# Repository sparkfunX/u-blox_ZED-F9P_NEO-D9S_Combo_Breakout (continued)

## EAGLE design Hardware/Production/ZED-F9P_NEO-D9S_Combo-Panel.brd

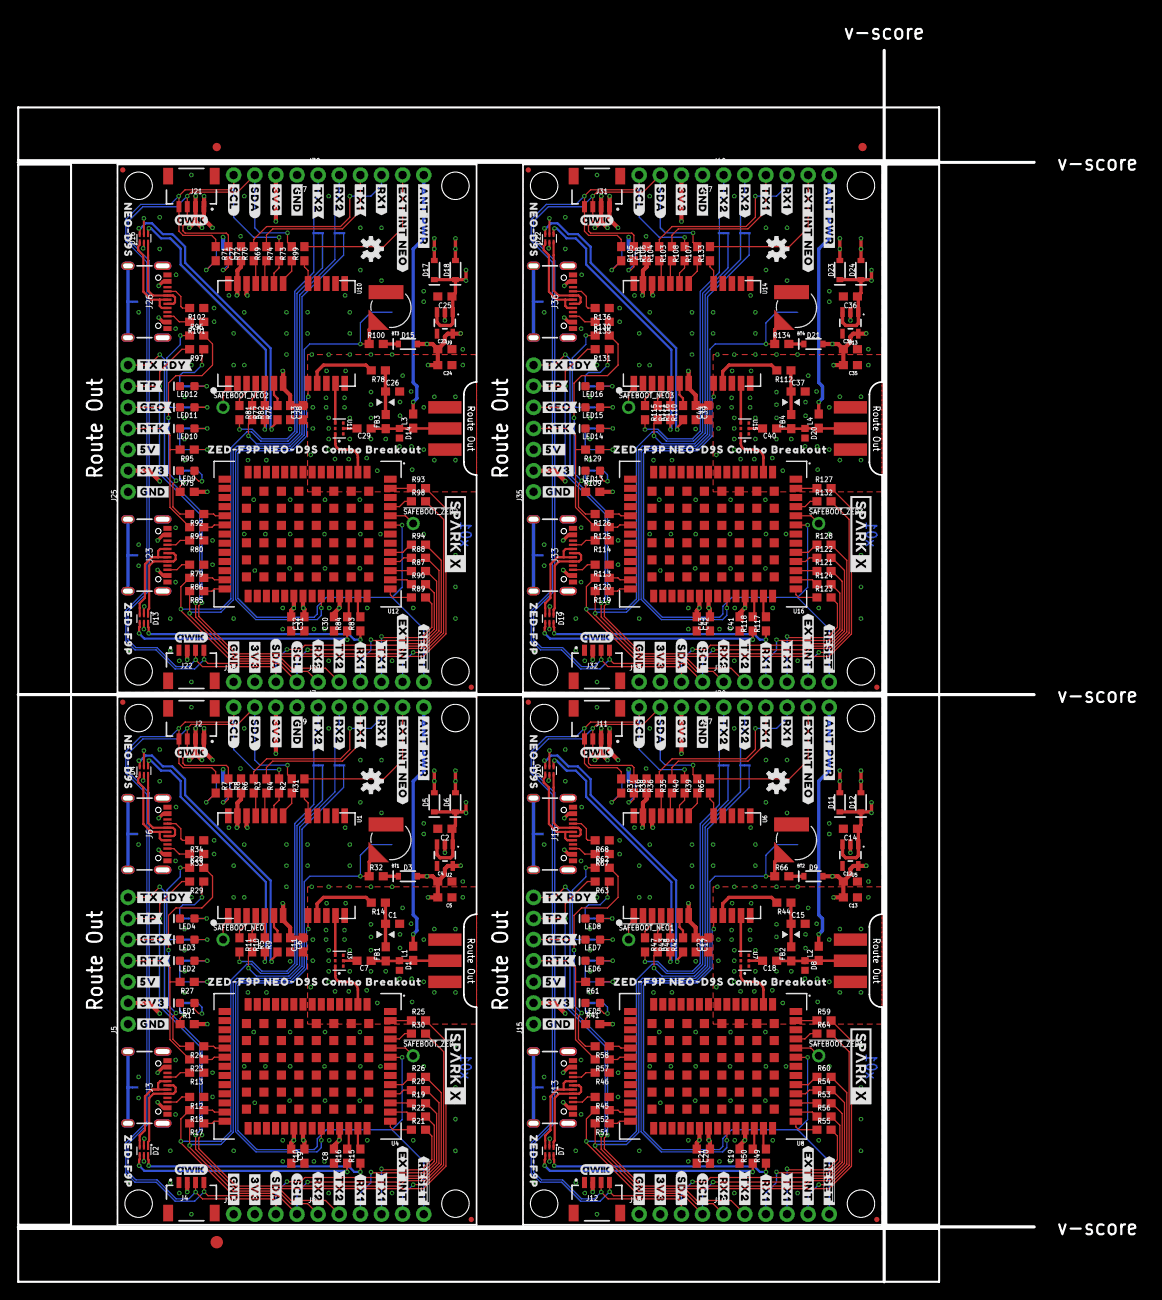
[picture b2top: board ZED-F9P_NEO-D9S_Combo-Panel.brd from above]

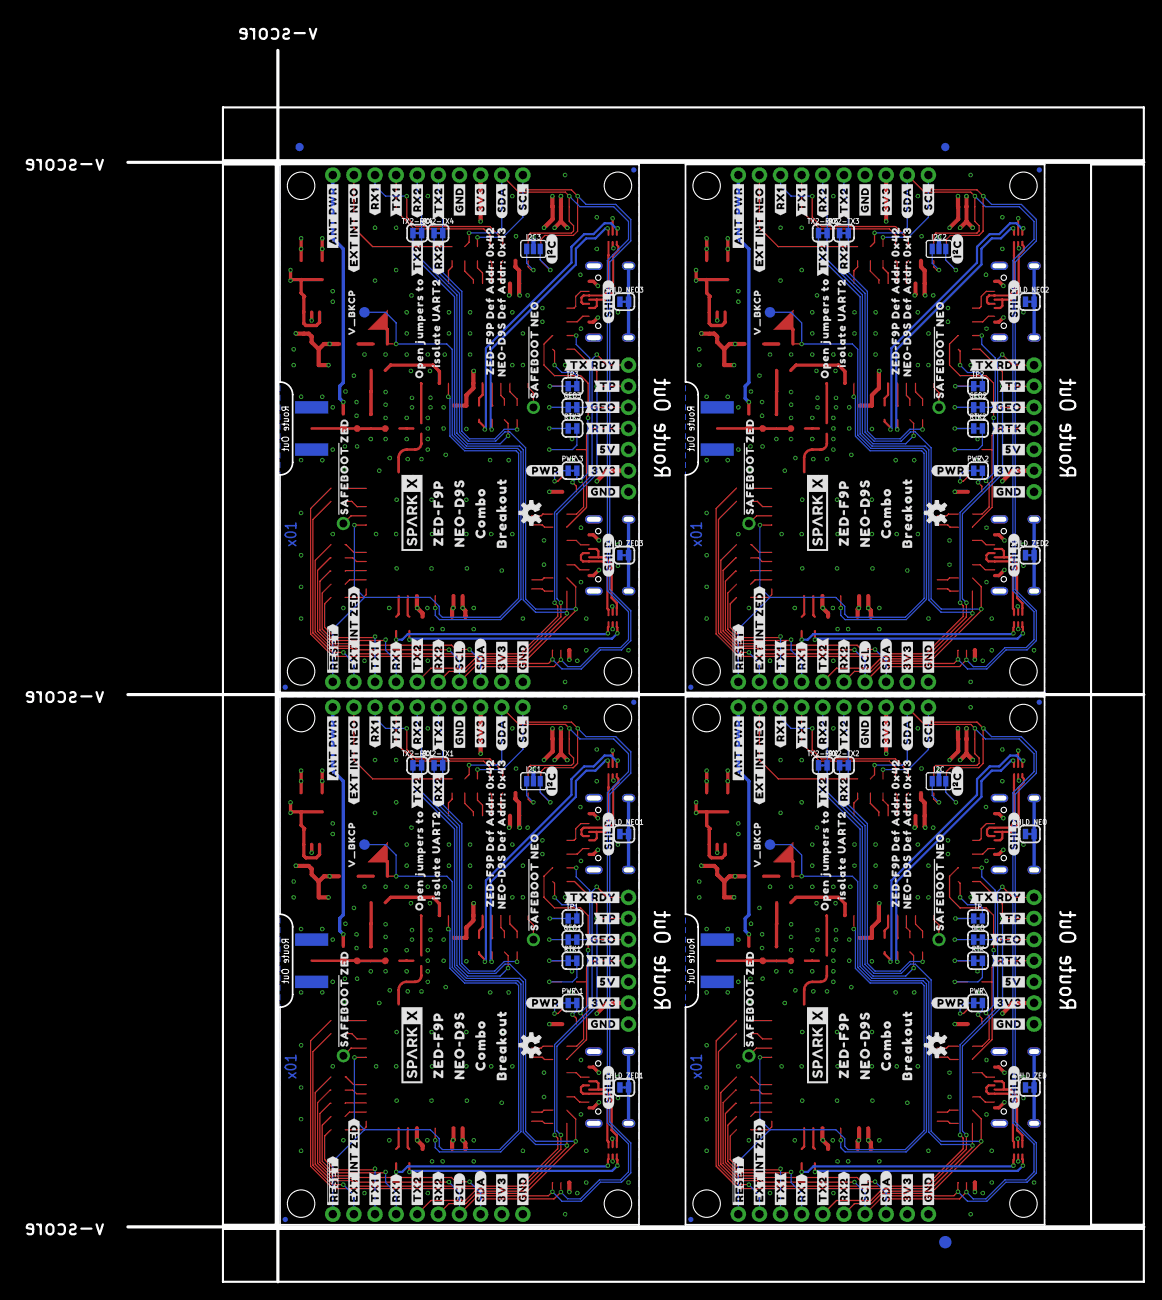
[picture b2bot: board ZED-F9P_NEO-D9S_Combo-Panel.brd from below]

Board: 4 copper layers, 122.2 x 148.1 mm, 694 parts (235 on the bottom side), 316 nets.

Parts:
!SAFEBOOT_NEO!, !SAFEBOOT_NEO!1, !SAFEBOOT_NEO!2, !SAFEBOOT_NEO!3: TEST-POINTPOGO_PTH; 1X01_NO_SILK
!SAFEBOOT_ZED!, !SAFEBOOT_ZED!1, !SAFEBOOT_ZED!2, !SAFEBOOT_ZED!3: TEST-POINTPOGO_PTH; 1X01_NO_SILK
BT1, BT2, BT3, BT4: RELOWABLE_BATTERY_MS421R; MS421R_IV03E
C1, C7, C15, C18, C26, C29, C37, C40: 47pF; 0603
C2, C3, C4, C6, C8, C9, C12, C14, C16, C17, C19, C20, C23, C25, C27, C28, C30, C31, C34, C36, C38, C39, C41, C42: 1.0uF; 0603
C5, C10, C11, C13, C21, C22, C24, C32, C33, C35, C43, C44: 0.1uF; 0603
D1, D8, D14, D20: PESD0402-0402; 0402
D2, D4, D7, D10, D13, D16, D19, D22: PRTR5V0U2F; SOT886
D3, D9, D15, D21: 0.5A/40V/420mV; SOD-323
D5, D6, D11, D12, D17, D18, D23, D24: 1A/23V/620mV; SOD-323
E$1, E$2, E$3, E$4: FIDUCIAL-1X2
E$5, E$6: FIDUCIAL-1.5X3
FB1, FB2, FB3, FB4: 30Ω/1.8A; 0603
GEO, GEO1, GEO2, GEO3: JUMPER-SMT_2_NC_TRACE_SILK; SMT-JUMPER_2_NC_TRACE_SILK
I2C, I2C1, I2C2, I2C3: JUMPER-SMT_3_NO_SILK; SMT-JUMPER_3_NO_SILK
J1, J14, J24, J34: ANTENNA-SMA-GROUNDEDEDGE_SMA; SMA-EDGE
J2, J4, J11, J12, J21, J22, J31, J32: Qwiic Right Angle; JST04_1MM_RA
J3, J6, J13, J16, J23, J26, J33, J36: USB Female Type C Connector; USB-C-16P_4LAYER-PADS
J5, J15, J25, J35: 1X07_NO_SILK
J7, J8, J19, J20, J29, J30, J39, J40: 1X06_NO_SILK
J9, J10, J17, J18, J27, J28, J37, J38: 1X04_NO_SILK
JP1, JP2, JP7, JP8, JP9, JP10, JP15, JP16, JP17, JP18, JP24, JP25, JP31, JP41, JP91, JP101: STAND-OFF
JP3, JP4, JP5, JP6, JP11, JP12, JP13, JP14, JP19, JP20, JP21, JP22, JP23, JP61, JP71, JP81: FIDUCIALUFIDUCIAL; MICRO-FIDUCIAL
L1, L2, L3, L4: DNP; 0603_NO-CREAM
LED1, LED5, LED9, LED13: RED; LED-0603
LED2, LED3, LED4, LED6, LED7, LED8, LED10, LED11, LED12, LED14, LED15, LED16: BLUE; LED-0603
LOGO1, LOGO2, LOGO3, LOGO4, LOGO5, LOGO6, LOGO7, LOGO8: OSHW-LOGOS; OSHW-LOGO-S
PWR\, PWR\1, PWR\2, PWR\3: JUMPER-SMT_2_NC_TRACE_SILK; SMT-JUMPER_2_NC_TRACE_SILK
R1, R27, R28, R29, R41, R61, R62, R63, R75, R95, R96, R97, R109, R129, R130, R131: 1k; 0603
R2, R3, R4, R5, R6, R11, R17, R18, R19, R20, R21, R22, R23, R24, R25, R26, R30, R31, R35, R36, R39, R40, R47, R48, R51, R52, R53, R54, R55, R56, R57, R58, R59, R60, R64, R65, R69, R70, R73, R74, R81, R82, R85, R86, R87, R88, R89, R90, R91, R92, R93, R94, R98, R99, R103, R104, R107, R108, R115, R116, R119, R120, R121, R122, R123, R124, R125, R126, R127, R128, R132, R133: 33; 0603
R7, R8, R37, R38, R71, R72, R105, R106: 2.2k; 0603
R9, R10, R15, R16, R42, R43, R49, R50, R76, R77, R83, R84, R110, R111, R117, R118: 27; 0603
R12, R13, R33, R34, R45, R46, R67, R68, R79, R80, R101, R102, R113, R114, R135, R136: 5.1k; 0603
R14, R44, R78, R112: 10; 0603
R32, R66, R100, R134: 3.3k; 0603
RTK, RTK1, RTK2, RTK3: JUMPER-SMT_2_NC_TRACE_SILK; SMT-JUMPER_2_NC_TRACE_SILK
RX2-TX1, RX2-TX2, RX2-TX3, RX2-TX4: JUMPER-SMT_2_NC_TRACE_SILK; SMT-JUMPER_2_NC_TRACE_SILK
SHLD_NEO, SHLD_NEO1, SHLD_NEO2, SHLD_NEO3: JUMPER-SMT_2_NC_TRACE_SILK; SMT-JUMPER_2_NC_TRACE_SILK
SHLD_ZED, SHLD_ZED1, SHLD_ZED2, SHLD_ZED3: JUMPER-SMT_2_NC_TRACE_SILK; SMT-JUMPER_2_NC_TRACE_SILK
TP, TP1, TP2, TP3: JUMPER-SMT_2_NC_TRACE_SILK; SMT-JUMPER_2_NC_TRACE_SILK
TX2-RX1, TX2-RX2, TX2-RX3, TX2-RX4: JUMPER-SMT_2_NC_TRACE_SILK; SMT-JUMPER_2_NC_TRACE_SILK
U1, U6, U10, U14: U-BLOX_NEO-D9S-00B; NEO-M9N/M8T/M8U/D9S
U2, U5, U9, U13: 3.3V; SOT23-5
U3, U7, U11, U15: POWER-DIVIDER; PD0922J5050S2HF_ANA
U4, U8, U12, U16: U-BLOX_ZED-F9P; ZED-F9P
U$1, U$2, U$3, U$80, U$81, U$82, U$158, U$159, U$160, U$236, U$237, U$238: #GND#0
U$4, U$5, U$6, U$83, U$84, U$85, U$161, U$162, U$163, U$239, U$240, U$241: #GND#1
U$7, U$53, U$96, U$127, U$174, U$205, U$252, U$283: #SHLD#0
U$8, U$10, U$128, U$129, U$206, U$207, U$284, U$285: #SDA#0
U$9, U$13, U$132, U$133, U$210, U$211, U$288, U$289: #SCL#0
U$11, U$12, U$130, U$131, U$208, U$209, U$286, U$287: #SDA#1
U$14, U$38, U$79, U$97, U$157, U$175, U$235, U$253: QWIIC_4MM
U$15, U$30, U$134, U$135, U$212, U$213, U$290, U$291: #SCL#1
U$16, U$101, U$179, U$257: #RTK#0
U$17, U$102, U$180, U$258: #RTK#1
U$18, U$103, U$181, U$259: #GEO#0
U$19, U$104, U$182, U$260: #GEO#1
U$20, U$86, U$164, U$242: #5V#0
U$21, U$87, U$165, U$243: #5V#6
U$22, U$23, U$56, U$88, U$89, U$98, U$166, U$167, U$176, U$244, U$245, U$254: #3V3#0
U$24, U$25, U$70, U$90, U$91, U$147, U$168, U$169, U$225, U$246, U$247, U$303: #3V3#4
U$26, U$105, U$183, U$261: #TP#0
U$27, U$106, U$184, U$262: #TP#1
U$28, U$107, U$185, U$263: #TX_RDY#0
U$29, U$108, U$186, U$264: #TX_RDY#1
U$31, U$39, U$40, U$113, U$114, U$136, U$191, U$192, U$214, U$269, U$270, U$292: #TX2#0
U$32, U$34, U$35, U$109, U$110, U$137, U$187, U$188, U$215, U$265, U$266, U$293: #RX2#0
U$33, U$144, U$222, U$300: OPEN_JUMPERS_TO0
U$36, U$37, U$111, U$112, U$189, U$190, U$267, U$268: #RX2#3
U$41, U$42, U$115, U$116, U$193, U$194, U$271, U$272: #TX2#3
U$43, U$44, U$117, U$118, U$195, U$196, U$273, U$274: #RX1#0
U$45, U$92, U$170, U$248: ##RESET##0
U$46, U$93, U$171, U$249: ##RESET##1
U$47, U$94, U$172, U$250: #EXT_INT#0
U$48, U$152, U$230, U$308: #EXT_INT_ZED#0
U$49, U$50, U$119, U$120, U$197, U$198, U$275, U$276: #RX1#2
U$51, U$57, U$121, U$122, U$199, U$200, U$277, U$278: #TX1#0
U$52, U$95, U$173, U$251: #I�C#0
U$54, U$145, U$223, U$301: ISOLATE_UART21
U$55, U$140, U$218, U$296: NEO#D9S0
U$58, U$99, U$177, U$255: #ANT_PWR#0
U$59, U$100, U$178, U$256: #ANT_PWR#1
U$60, U$61, U$123, U$124, U$201, U$202, U$279, U$280: #TX1#2
U$62, U$125, U$203, U$281: #EXT_INT_NEO#0
U$63, U$126, U$204, U$282: #EXT_INT_NEO#1
U$64, U$138, U$216, U$294: ZED#F9P0
U$65, U$139, U$217, U$295: ZED#F9P10
U$66, U$141, U$219, U$297: NEO#D9S10
U$67, U$142, U$220, U$298: COMBO10
U$68, U$143, U$221, U$299: BREAKOUT11
U$69, U$146, U$224, U$302: #PWR#0
U$71, U$148, U$226, U$304: #SAFEBOOT#_NEO0
U$72, U$149, U$227, U$305: #SAFEBOOT#_ZED0
U$73, U$150, U$228, U$306: NEO#D9S_DEF_ADDR#_0X4310
U$74, U$151, U$229, U$307: ZED#F9P_DEF_ADDR#_0X420
U$75, U$153, U$231, U$309: ZED#F9P_NEO#D9S_COMBO_BREAKOUT0
U$76, U$154, U$232, U$310: V_BKCP0
U$77, U$78, U$155, U$156, U$233, U$234, U$311, U$312: SPARKX-LOGO4; SPARKX-MEDIUM
V_BKCP, V_BKCP1, V_BKCP2, V_BKCP3: TEST-POINT3X5; PAD.03X.05

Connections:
3.3V: C3.1, C4.1, C5.2, C6.1, C8.2, C9.1, C10.2, C11.2, D3.A, I2C.2, J2.2, J4.2, J5.2, J9.2, J10.2, R1.2, U1.7, U1.22, U1.23, U2.5, U4.33, U4.34, U4.38
3.3V1: C12.1, C13.2, C16.1, C17.1, C19.2, C20.1, C21.2, C22.2, D9.A, I2C1.2, J11.2, J12.2, J15.2, J17.2, J18.2, R41.2, U5.5, U6.7, U6.22, U6.23, U8.33, U8.34, U8.38
3.3V2: C23.1, C24.2, C27.1, C28.1, C30.2, C31.1, C32.2, C33.2, D15.A, I2C2.2, J21.2, J22.2, J25.2, J27.2, J28.2, R75.2, U9.5, U10.7, U10.22, U10.23, U12.33, U12.34, U12.38
3.3V3: C34.1, C35.2, C38.1, C39.1, C41.2, C42.1, C43.2, C44.2, D21.A, I2C3.2, J31.2, J32.2, J35.2, J37.2, J38.2, R109.2, U13.5, U14.7, U14.22, U14.23, U16.33, U16.34, U16.38
5V: C2.1, D5.C, D6.C, J5.3, U2.1, U2.3
5V1: C14.1, D11.C, D12.C, J15.3, U5.1, U5.3
5V2: C25.1, D17.C, D18.C, J25.3, U9.1, U9.3
5V3: C36.1, D23.C, D24.C, J35.3, U13.1, U13.3
!RESET!: J8.6, U1.8, U4.49
!RESET!1: J19.6, U6.8, U8.49
!RESET!2: J29.6, U10.8, U12.49
!RESET!3: J39.6, U14.8, U16.49
!SAFEBOOT_NEO!: !SAFEBOOT_NEO!.1, U1.1
!SAFEBOOT_NEO!1: !SAFEBOOT_NEO!1.1, U6.1
!SAFEBOOT_NEO!2: !SAFEBOOT_NEO!2.1, U10.1
!SAFEBOOT_NEO!3: !SAFEBOOT_NEO!3.1, U14.1
!SAFEBOOT_ZED!: !SAFEBOOT_ZED!.1, U4.50
!SAFEBOOT_ZED!1: !SAFEBOOT_ZED!1.1, U8.50
!SAFEBOOT_ZED!2: !SAFEBOOT_ZED!2.1, U12.50
!SAFEBOOT_ZED!3: !SAFEBOOT_ZED!3.1, U16.50
ANT: C7.2, U3.2
ANT1: C18.2, U7.2
ANT2: C29.2, U11.2
ANT3: C40.2, U15.2
ANT_NEO: U1.11, U3.4
ANT_NEO1: U6.11, U7.4
ANT_NEO2: U10.11, U11.4
ANT_NEO3: U14.11, U15.4
ANT_PWR: J7.6, L1.2
ANT_PWR1: J20.6, L2.2
ANT_PWR2: J30.6, L3.2
ANT_PWR3: J40.6, L4.2
ANT_VCC: C1.1, FB1.2, R14.1
ANT_VCC1: C15.1, FB2.2, R44.1
ANT_VCC2: C26.1, FB3.2, R78.1
ANT_VCC3: C37.1, FB4.2, R112.1
ANT_ZED: U3.6, U4.2
ANT_ZED1: U7.6, U8.2
ANT_ZED2: U11.6, U12.2
ANT_ZED3: U15.6, U16.2
D+_NEO: D4.6, R9.1
D+_NEO1: D10.6, R42.1
D+_NEO2: D16.6, R76.1
D+_NEO3: D22.6, R110.1
D+_ZED: D2.6, R15.1
D+_ZED1: D7.6, R49.1
D+_ZED2: D13.6, R83.1
D+_ZED3: D19.6, R117.1
D-_NEO: D4.4, R10.1
D-_NEO1: D10.4, R43.1
D-_NEO2: D16.4, R77.1
D-_NEO3: D22.4, R111.1
D-_ZED: D2.4, R16.1
D-_ZED1: D7.4, R50.1
D-_ZED2: D13.4, R84.1
D-_ZED3: D19.4, R118.1
EXT_INT_NEO: J7.5, R31.2
EXT_INT_NEO1: J20.5, R65.2
EXT_INT_NEO2: J30.5, R99.2
EXT_INT_NEO3: J40.5, R133.2
EXT_INT_ZED: J8.5, R30.2
EXT_INT_ZED1: J19.5, R64.2
EXT_INT_ZED2: J29.5, R98.2
EXT_INT_ZED3: J39.5, R132.2
GEO: J5.5, R24.2, R28.2
GEO1: J15.5, R58.2, R62.2
GEO2: J25.5, R92.2, R96.2
GEO3: J35.5, R126.2, R130.2
GND: BT1.-, C1.2, C2.2, C3.2, C4.2, C5.1, C6.2, C8.1, C9.2, C10.1, C11.1, D1.2, D2.2, D4.2, J1.GND@0, J1.GND@1, J1.GND@2, J1.GND@3, J2.1, J3.GND, J3.GND2, J4.1, J5.1, J6.GND, J6.GND2, J9.1, J10.1, LED1.C, LED2.C, LED3.C, LED4.C, R12.1, R13.1, R33.1, R34.1, SHLD_NEO.1, SHLD_ZED.1, U1.10, U1.12, U1.13, U1.24, U2.2, U3.1, U3.3, U3.5, U4.1, U4.3, U4.12, U4.14, U4.32, U4.37, U4.41, U4.48, U4.55, U4.56, U4.57, U4.58, U4.59, U4.60, U4.61, U4.62, U4.63, U4.64, U4.65, U4.66, U4.67, U4.68, U4.69, U4.70, U4.71, U4.72, U4.73, U4.74, U4.75, U4.76, U4.77, U4.78, U4.79, U4.80, U4.81, U4.82, U4.83, U4.84, U4.85, U4.86, U4.87, U4.88, U4.89, U4.90, U4.91, U4.92, U4.93, U4.94, U4.95, U4.96, U4.97, U4.98, U4.99, U4.100, U4.101, U4.102
GND1: BT2.-, C12.2, C13.1, C14.2, C15.2, C16.2, C17.2, C19.1, C20.2, C21.1, C22.1, D7.2, D8.2, D10.2, J11.1, J12.1, J13.GND, J13.GND2, J14.GND@0, J14.GND@1, J14.GND@2, J14.GND@3, J15.1, J16.GND, J16.GND2, J17.1, J18.1, LED5.C, LED6.C, LED7.C, LED8.C, R45.1, R46.1, R67.1, R68.1, SHLD_NEO1.1, SHLD_ZED1.1, U5.2, U6.10, U6.12, U6.13, U6.24, U7.1, U7.3, U7.5, U8.1, U8.3, U8.12, U8.14, U8.32, U8.37, U8.41, U8.48, U8.55, U8.56, U8.57, U8.58, U8.59, U8.60, U8.61, U8.62, U8.63, U8.64, U8.65, U8.66, U8.67, U8.68, U8.69, U8.70, U8.71, U8.72, U8.73, U8.74, U8.75, U8.76, U8.77, U8.78, U8.79, U8.80, U8.81, U8.82, U8.83, U8.84, U8.85, U8.86, U8.87, U8.88, U8.89, U8.90, U8.91, U8.92, U8.93, U8.94, U8.95, U8.96, U8.97, U8.98, U8.99, U8.100, U8.101, U8.102
GND2: BT3.-, C23.2, C24.1, C25.2, C26.2, C27.2, C28.2, C30.1, C31.2, C32.1, C33.1, D13.2, D14.2, D16.2, J21.1, J22.1, J23.GND, J23.GND2, J24.GND@0, J24.GND@1, J24.GND@2, J24.GND@3, J25.1, J26.GND, J26.GND2, J27.1, J28.1, LED9.C, LED10.C, LED11.C, LED12.C, R79.1, R80.1, R101.1, R102.1, SHLD_NEO2.1, SHLD_ZED2.1, U9.2, U10.10, U10.12, U10.13, U10.24, U11.1, U11.3, U11.5, U12.1, U12.3, U12.12, U12.14, U12.32, U12.37, U12.41, U12.48, U12.55, U12.56, U12.57, U12.58, U12.59, U12.60, U12.61, U12.62, U12.63, U12.64, U12.65, U12.66, U12.67, U12.68, U12.69, U12.70, U12.71, U12.72, U12.73, U12.74, U12.75, U12.76, U12.77, U12.78, U12.79, U12.80, U12.81, U12.82, U12.83, U12.84, U12.85, U12.86, U12.87, U12.88, U12.89, U12.90, U12.91, U12.92, U12.93, U12.94, U12.95, U12.96, U12.97, U12.98, U12.99, U12.100, U12.101, U12.102
GND3: BT4.-, C34.2, C35.1, C36.2, C37.2, C38.2, C39.2, C41.1, C42.2, C43.1, C44.1, D19.2, D20.2, D22.2, J31.1, J32.1, J33.GND, J33.GND2, J34.GND@0, J34.GND@1, J34.GND@2, J34.GND@3, J35.1, J36.GND, J36.GND2, J37.1, J38.1, LED13.C, LED14.C, LED15.C, LED16.C, R113.1, R114.1, R135.1, R136.1, SHLD_NEO3.1, SHLD_ZED3.1, U13.2, U14.10, U14.12, U14.13, U14.24, U15.1, U15.3, U15.5, U16.1, U16.3, U16.12, U16.14, U16.32, U16.37, U16.41, U16.48, U16.55, U16.56, U16.57, U16.58, U16.59, U16.60, U16.61, U16.62, U16.63, U16.64, U16.65, U16.66, U16.67, U16.68, U16.69, U16.70, U16.71, U16.72, U16.73, U16.74, U16.75, U16.76, U16.77, U16.78, U16.79, U16.80, U16.81, U16.82, U16.83, U16.84, U16.85, U16.86, U16.87, U16.88, U16.89, U16.90, U16.91, U16.92, U16.93, U16.94, U16.95, U16.96, U16.97, U16.98, U16.99, U16.100, U16.101, U16.102
unnamed: PWR\.2, R1.1
unnamed: R3.1, U1.20
unnamed: R2.1, U1.18
unnamed: R4.1, U1.19
unnamed: I2C.1, R8.2
unnamed: R6.1, U1.21
unnamed: J3.B5, R12.2
unnamed: I2C.3, R7.2
unnamed: J3.A5, R13.2
unnamed: LED1.A, PWR\.1
unnamed: R9.2, U1.6
unnamed: R10.2, U1.5
unnamed: D3.C, R32.2
unnamed: R11.1, U1.3
unnamed: R5.1, U1.4
unnamed: R15.2, U4.40
unnamed: R16.2, U4.39
unnamed: R19.1, U4.44
unnamed: R20.1, U4.45
unnamed: R21.1, U4.42
unnamed: R22.1, U4.43
unnamed: R26.1, U4.46
unnamed: LED2.A, RTK.1
unnamed: R17.1, U4.27
unnamed: R18.1, U4.26
unnamed: GEO.1, LED3.A
unnamed: LED4.A, TP.1
unnamed: R27.1, RTK.2
unnamed: GEO.2, R28.1
unnamed: R29.1, TP.2
unnamed: R30.1, U4.51
unnamed: R31.1, U1.17
unnamed: J6.B5, R33.2
unnamed: J6.A5, R34.2
unnamed: R23.1, U4.20
unnamed: R24.1, U4.19
unnamed: R25.1, U4.53
unnamed: I2C1.1, R38.2
unnamed: I2C1.3, R37.2
unnamed: R42.2, U6.6
unnamed: R43.2, U6.5
unnamed: J13.B5, R45.2
unnamed: J13.A5, R46.2
unnamed: R47.1, U6.3
unnamed: R48.1, U6.4
unnamed: R35.1, U6.20
unnamed: R36.1, U6.21
unnamed: R39.1, U6.18
unnamed: R40.1, U6.19
unnamed: R49.2, U8.40
unnamed: R50.2, U8.39
unnamed: R53.1, U8.44
unnamed: R54.1, U8.45
unnamed: R55.1, U8.42
unnamed: R56.1, U8.43
unnamed: R51.1, U8.27
unnamed: R52.1, U8.26
unnamed: R60.1, U8.46
unnamed: LED6.A, RTK1.1
unnamed: GEO1.1, LED7.A
unnamed: LED8.A, TP1.1
unnamed: R61.1, RTK1.2
unnamed: GEO1.2, R62.1
unnamed: R63.1, TP1.2
unnamed: R57.1, U8.20
unnamed: R58.1, U8.19
unnamed: R59.1, U8.53
unnamed: R64.1, U8.51
unnamed: R65.1, U6.17
unnamed: D9.C, R66.2
unnamed: J16.B5, R67.2
unnamed: J16.A5, R68.2
unnamed: PWR\1.2, R41.1
unnamed: LED5.A, PWR\1.1
unnamed: I2C2.1, R72.2
unnamed: I2C2.3, R71.2
unnamed: R76.2, U10.6
unnamed: R77.2, U10.5
unnamed: J23.B5, R79.2
unnamed: J23.A5, R80.2
unnamed: R81.1, U10.3
unnamed: R82.1, U10.4
unnamed: R69.1, U10.20
unnamed: R70.1, U10.21
unnamed: R73.1, U10.18
unnamed: R74.1, U10.19
unnamed: R83.2, U12.40
unnamed: R84.2, U12.39
unnamed: R87.1, U12.44
unnamed: R88.1, U12.45
unnamed: R89.1, U12.42
unnamed: R90.1, U12.43
unnamed: R85.1, U12.27
unnamed: R86.1, U12.26
unnamed: R94.1, U12.46
unnamed: LED10.A, RTK2.1
unnamed: GEO2.1, LED11.A
unnamed: LED12.A, TP2.1
unnamed: R95.1, RTK2.2
unnamed: GEO2.2, R96.1
unnamed: R97.1, TP2.2
unnamed: R91.1, U12.20
unnamed: R92.1, U12.19
unnamed: R93.1, U12.53
unnamed: R98.1, U12.51
unnamed: R99.1, U10.17
unnamed: D15.C, R100.2
unnamed: J26.B5, R101.2
unnamed: J26.A5, R102.2
unnamed: PWR\2.2, R75.1
unnamed: LED9.A, PWR\2.1
unnamed: I2C3.1, R106.2
unnamed: I2C3.3, R105.2
unnamed: R110.2, U14.6
unnamed: R111.2, U14.5
unnamed: J33.B5, R113.2
unnamed: J33.A5, R114.2
unnamed: R115.1, U14.3
unnamed: R116.1, U14.4
unnamed: R103.1, U14.20
unnamed: R104.1, U14.21
unnamed: R107.1, U14.18
unnamed: R108.1, U14.19
unnamed: R117.2, U16.40
unnamed: R118.2, U16.39
unnamed: R121.1, U16.44
unnamed: R122.1, U16.45
unnamed: R123.1, U16.42
unnamed: R124.1, U16.43
unnamed: R119.1, U16.27
unnamed: R120.1, U16.26
unnamed: R128.1, U16.46
unnamed: LED14.A, RTK3.1
unnamed: GEO3.1, LED15.A
unnamed: LED16.A, TP3.1
unnamed: R129.1, RTK3.2
unnamed: GEO3.2, R130.1
unnamed: R131.1, TP3.2
unnamed: R125.1, U16.20
unnamed: R126.1, U16.19
unnamed: R127.1, U16.53
unnamed: R132.1, U16.51
unnamed: R133.1, U14.17
unnamed: D21.C, R134.2
unnamed: J36.B5, R135.2
unnamed: J36.A5, R136.2
unnamed: PWR\3.2, R109.1
unnamed: LED13.A, PWR\3.1
RTK: J5.4, R23.2, R27.2
RTK1: J15.4, R57.2, R61.2
RTK2: J25.4, R91.2, R95.2
RTK3: J35.4, R125.2, R129.2
RXD1_NEO: J7.4, R6.2
RXD1_NEO1: J20.4, R36.2
RXD1_NEO2: J30.4, R70.2
RXD1_NEO3: J40.4, R104.2
RXD1_ZED: J8.3, R22.2
RXD1_ZED1: J19.3, R56.2
RXD1_ZED2: J29.3, R90.2
RXD1_ZED3: J39.3, R124.2
RXD2_NEO: J7.2, R5.2, TX2-RX2.2
RXD2_NEO1: J20.2, R48.2, TX2-RX1.2
RXD2_NEO2: J30.2, R82.2, TX2-RX3.2
RXD2_NEO3: J40.2, R116.2, TX2-RX4.2
RXD2_ZED: J8.1, R18.2, RX2-TX2.1
RXD2_ZED1: J19.1, R52.2, RX2-TX1.1
RXD2_ZED2: J29.1, R86.2, RX2-TX3.1
RXD2_ZED3: J39.1, R120.2, RX2-TX4.1
SCL: J2.4, J4.4, J9.4, J10.4, R4.2, R7.1, R20.2
SCL1: J11.4, J12.4, J17.4, J18.4, R37.1, R40.2, R54.2
SCL2: J21.4, J22.4, J27.4, J28.4, R71.1, R74.2, R88.2
SCL3: J31.4, J32.4, J37.4, J38.4, R105.1, R108.2, R122.2
SDA: J2.3, J4.3, J9.3, J10.3, R2.2, R8.1, R19.2
SDA1: J11.3, J12.3, J17.3, J18.3, R38.1, R39.2, R53.2
SDA2: J21.3, J22.3, J27.3, J28.3, R72.1, R73.2, R87.2
SDA3: J31.3, J32.3, J37.3, J38.3, R106.1, R107.2, R121.2
SHIELD_NEO: J6.SHLD1, J6.SHLD2, J6.SHLD3, J6.SHLD4, SHLD_NEO.2
SHIELD_NEO1: J16.SHLD1, J16.SHLD2, J16.SHLD3, J16.SHLD4, SHLD_NEO1.2
SHIELD_NEO2: J26.SHLD1, J26.SHLD2, J26.SHLD3, J26.SHLD4, SHLD_NEO2.2
SHIELD_NEO3: J36.SHLD1, J36.SHLD2, J36.SHLD3, J36.SHLD4, SHLD_NEO3.2
SHIELD_ZED: J3.SHLD1, J3.SHLD2, J3.SHLD3, J3.SHLD4, SHLD_ZED.2
SHIELD_ZED1: J13.SHLD1, J13.SHLD2, J13.SHLD3, J13.SHLD4, SHLD_ZED1.2
SHIELD_ZED2: J23.SHLD1, J23.SHLD2, J23.SHLD3, J23.SHLD4, SHLD_ZED2.2
SHIELD_ZED3: J33.SHLD1, J33.SHLD2, J33.SHLD3, J33.SHLD4, SHLD_ZED3.2
SMA: C7.1, D1.1, FB1.1, J1.SIG, L1.1
SMA1: C18.1, D8.1, FB2.1, J14.SIG, L2.1
SMA2: C29.1, D14.1, FB3.1, J24.SIG, L3.1
SMA3: C40.1, D20.1, FB4.1, J34.SIG, L4.1
TP: J5.6, R25.2, R29.2
TP1: J15.6, R59.2, R63.2
TP2: J25.6, R93.2, R97.2
TP3: J35.6, R127.2, R131.2
TXD1_NEO: J7.3, R3.2
TXD1_NEO1: J20.3, R35.2
TXD1_NEO2: J30.3, R69.2
TXD1_NEO3: J40.3, R103.2
TXD1_ZED: J8.4, R21.2
TXD1_ZED1: J19.4, R55.2
TXD1_ZED2: J29.4, R89.2
TXD1_ZED3: J39.4, R123.2
TXD2_NEO: J7.1, R11.2, RX2-TX2.2
TXD2_NEO1: J20.1, R47.2, RX2-TX1.2
TXD2_NEO2: J30.1, R81.2, RX2-TX3.2
TXD2_NEO3: J40.1, R115.2, RX2-TX4.2
TXD2_ZED: J8.2, R17.2, TX2-RX2.1
TXD2_ZED1: J19.2, R51.2, TX2-RX1.1
TXD2_ZED2: J29.2, R85.2, TX2-RX3.1
TXD2_ZED3: J39.2, R119.2, TX2-RX4.1
TX_RDY: J5.7, R26.2
TX_RDY1: J15.7, R60.2
TX_RDY2: J25.7, R94.2
TX_RDY3: J35.7, R128.2
USB_D+: D2.1, J3.A6, J3.B6
USB_D+1: D4.1, J6.A6, J6.B6
USB_D+2: D7.1, J13.A6, J13.B6
USB_D+3: D10.1, J16.A6, J16.B6
USB_D+4: D13.1, J23.A6, J23.B6
USB_D+5: D16.1, J26.A6, J26.B6
USB_D+6: D19.1, J33.A6, J33.B6
USB_D+7: D22.1, J36.A6, J36.B6
USB_D-: D2.3, J3.A7, J3.B7
USB_D-1: D4.3, J6.A7, J6.B7
USB_D-2: D7.3, J13.A7, J13.B7
USB_D-3: D10.3, J16.A7, J16.B7
USB_D-4: D13.3, J23.A7, J23.B7
USB_D-5: D16.3, J26.A7, J26.B7
USB_D-6: D19.3, J33.A7, J33.B7
USB_D-7: D22.3, J36.A7, J36.B7
VCC_RF: R14.2, U1.9
VCC_RF1: R44.2, U6.9
VCC_RF2: R78.2, U10.9
VCC_RF3: R112.2, U14.9
V_BKCP: BT1.+, R32.1, U4.36, V_BKCP.1
V_BKCP1: BT2.+, R66.1, U8.36, V_BKCP1.1
V_BKCP2: BT3.+, R100.1, U12.36, V_BKCP2.1
V_BKCP3: BT4.+, R134.1, U16.36, V_BKCP3.1
V_USB: D2.5, D5.A, J3.VBUS1, J3.VBUS2
V_USB1: D7.5, D11.A, J13.VBUS1, J13.VBUS2
V_USB2: D13.5, D17.A, J23.VBUS1, J23.VBUS2
V_USB3: D19.5, D23.A, J33.VBUS1, J33.VBUS2
V_USB_1: D10.5, D12.A, J16.VBUS1, J16.VBUS2
V_USB_2: D4.5, D6.A, J6.VBUS1, J6.VBUS2
V_USB_3: D16.5, D18.A, J26.VBUS1, J26.VBUS2
V_USB_4: D22.5, D24.A, J36.VBUS1, J36.VBUS2

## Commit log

2022-05-26 x01 PCB
2022-05-26 Add IC-16658 GNSS Power Divider. Delete New_parts.lbr
2022-05-26 Use RF Library copy of IC-16658
2022-07-20 x02 PCB - inverts RTK LED
2022-08-29 Docs updates
2022-09-15 Docs images
2022-09-22 Add product image
2023-01-25 Docs updates for v3 of the GNSS library
2023-01-25 Add new 10m SMA cable
2023-01-25 Correct example code for v3
2023-01-25 Correct setVal for v3
2023-01-25 Deployed 7aa5d25 with MkDocs version: 1.4.2
